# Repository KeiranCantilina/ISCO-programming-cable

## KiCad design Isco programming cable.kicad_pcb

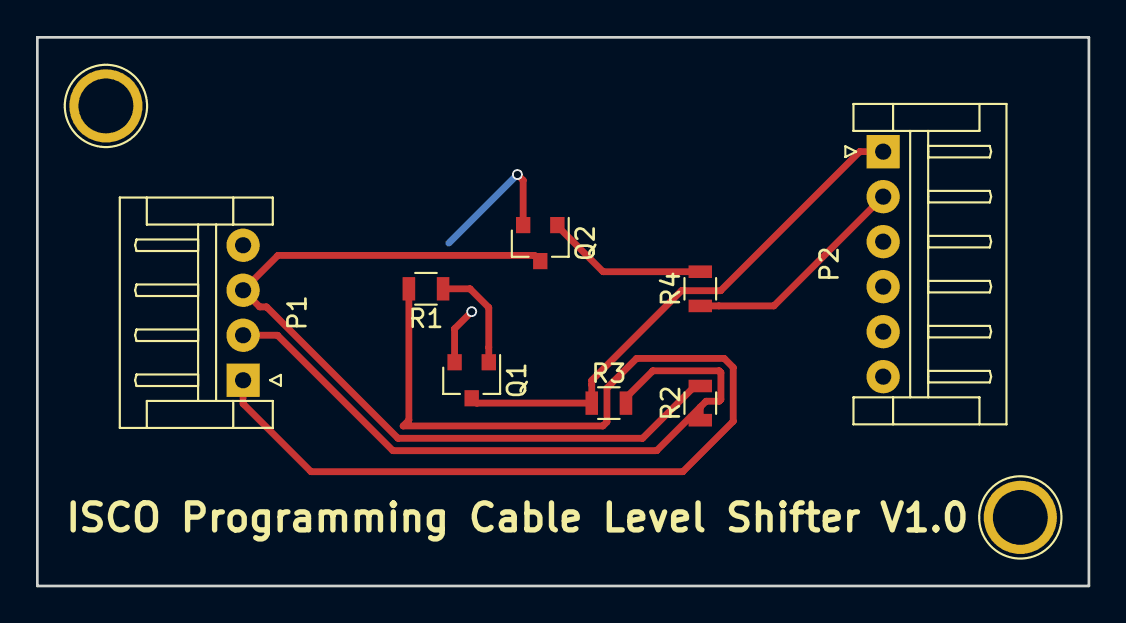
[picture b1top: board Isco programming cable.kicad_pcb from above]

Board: 2 copper layers, 58.4 x 30.5 mm, 8 parts (0 on the bottom side), 8 nets.

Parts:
P1: CONN_01X04; JST_EH_S04B-EH_04x2.50mm_Angled
P2: CONN_01X06; JST_EH_S06B-EH_06x2.50mm_Angled
Q1, Q2: MMBT3904; SOT-23
R1, R2, R3, R4: 5K; R_0805

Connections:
+5V(red): P1.2, R2.1, R3.2
GND(B): P1.4, P2.4, P2.5, Q1.2, Q2.2
unnamed: Q1.1, R1.1
unnamed: Q2.1, R4.2
RX(E): P2.1, Q1.3, R3.1
RX(yellow): P1.3, Q2.3, R2.2
TX(D): P2.2, R4.1
TX(orange): P1.1, R1.2

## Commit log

2018-06-27 Photos
